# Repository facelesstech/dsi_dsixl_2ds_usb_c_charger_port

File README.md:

# dsi_dsixl_2ds_usb_c_charger_port
dsi_dsixl_2ds_usb_c_charger_port

List of hardware you need

 * [6 pin USB C Port](https://www.aliexpress.com/item/32966491026.html?spm=a2g0o.productlist.0.0.40682b02dGnW8h&algo_pvid=d52f6c09-77d8-4ea5-9f91-3c1a38f8a389&algo_exp_id=d52f6c09-77d8-4ea5-9f91-3c1a38f8a389-0&pdp_ext_f=%7B%22sku_id%22%3A%2266546029161%22%7D&pdp_npi=2%40dis%21GBP%21%210.47%210.47%21%211.97%21%21%402100bdd716543375023874249e4539%2166546029161%21sea)
 * [5.1k 0603 SMD resistors x2](https://www.aliexpress.com/item/1005001436923851.html?spm=a2g0o.productlist.0.0.1dab6ecdFCRr6p&algo_pvid=8ccb23e2-83dc-4ed7-917b-6b67ea6ceffa&algo_exp_id=8ccb23e2-83dc-4ed7-917b-6b67ea6ceffa-0&pdp_ext_f=%7B%22sku_id%22%3A%2212000016109475033%22%7D&pdp_npi=2%40dis%21GBP%21%210.09%210.09%21%21%21%21%402100bde316543376141027916e302a%2112000016109475033%21sea)

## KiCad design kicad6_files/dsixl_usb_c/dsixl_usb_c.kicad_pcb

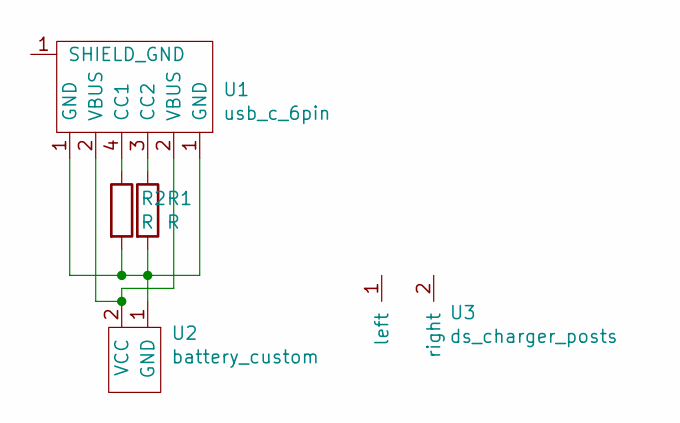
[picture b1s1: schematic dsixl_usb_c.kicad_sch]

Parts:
R1, R2: R; R_0603_1608Metric_Pad0.98x0.95mm_HandSolder
U1: usb_c_6pin; USB_C_6PIN_custom
U2: battery_custom; dsixl_charger_pins
U3: ds_charger_posts; dsixl_charger_posts

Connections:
unnamed: R1.1, U1.3 (CC2)
unnamed: R1.2, R2.2, U1.1 (GND), U2.1 (GND)
unnamed: R2.1, U1.4 (CC1)
unnamed: U1.2 (VBUS), U2.2 (VCC)

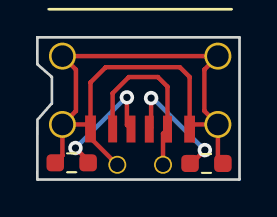
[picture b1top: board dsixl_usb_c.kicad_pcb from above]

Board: 2 copper layers, 11.2 x 7.9 mm, 5 parts (1 on the bottom side), 4 nets.

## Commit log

2023-03-27 added files
2023-03-27 added license
2023-03-27 added photo
2023-03-28 added links
2023-03-28 added links1
2023-08-08 added new 3d print files
